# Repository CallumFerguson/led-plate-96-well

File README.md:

# led-plate-96-well

control genetically engineered cells with light

## Description

PCB for running optogenetic experiments. Designed to shine light through the bottom of [clear bottom 96 well plates](https://www.thermofisher.com/order/catalog/product/152037) and activate light gated ion channels in genetically engineered cells.

Used for experiments in controlling cell maturation by changing the cell's resting membrane potential.

## PCB

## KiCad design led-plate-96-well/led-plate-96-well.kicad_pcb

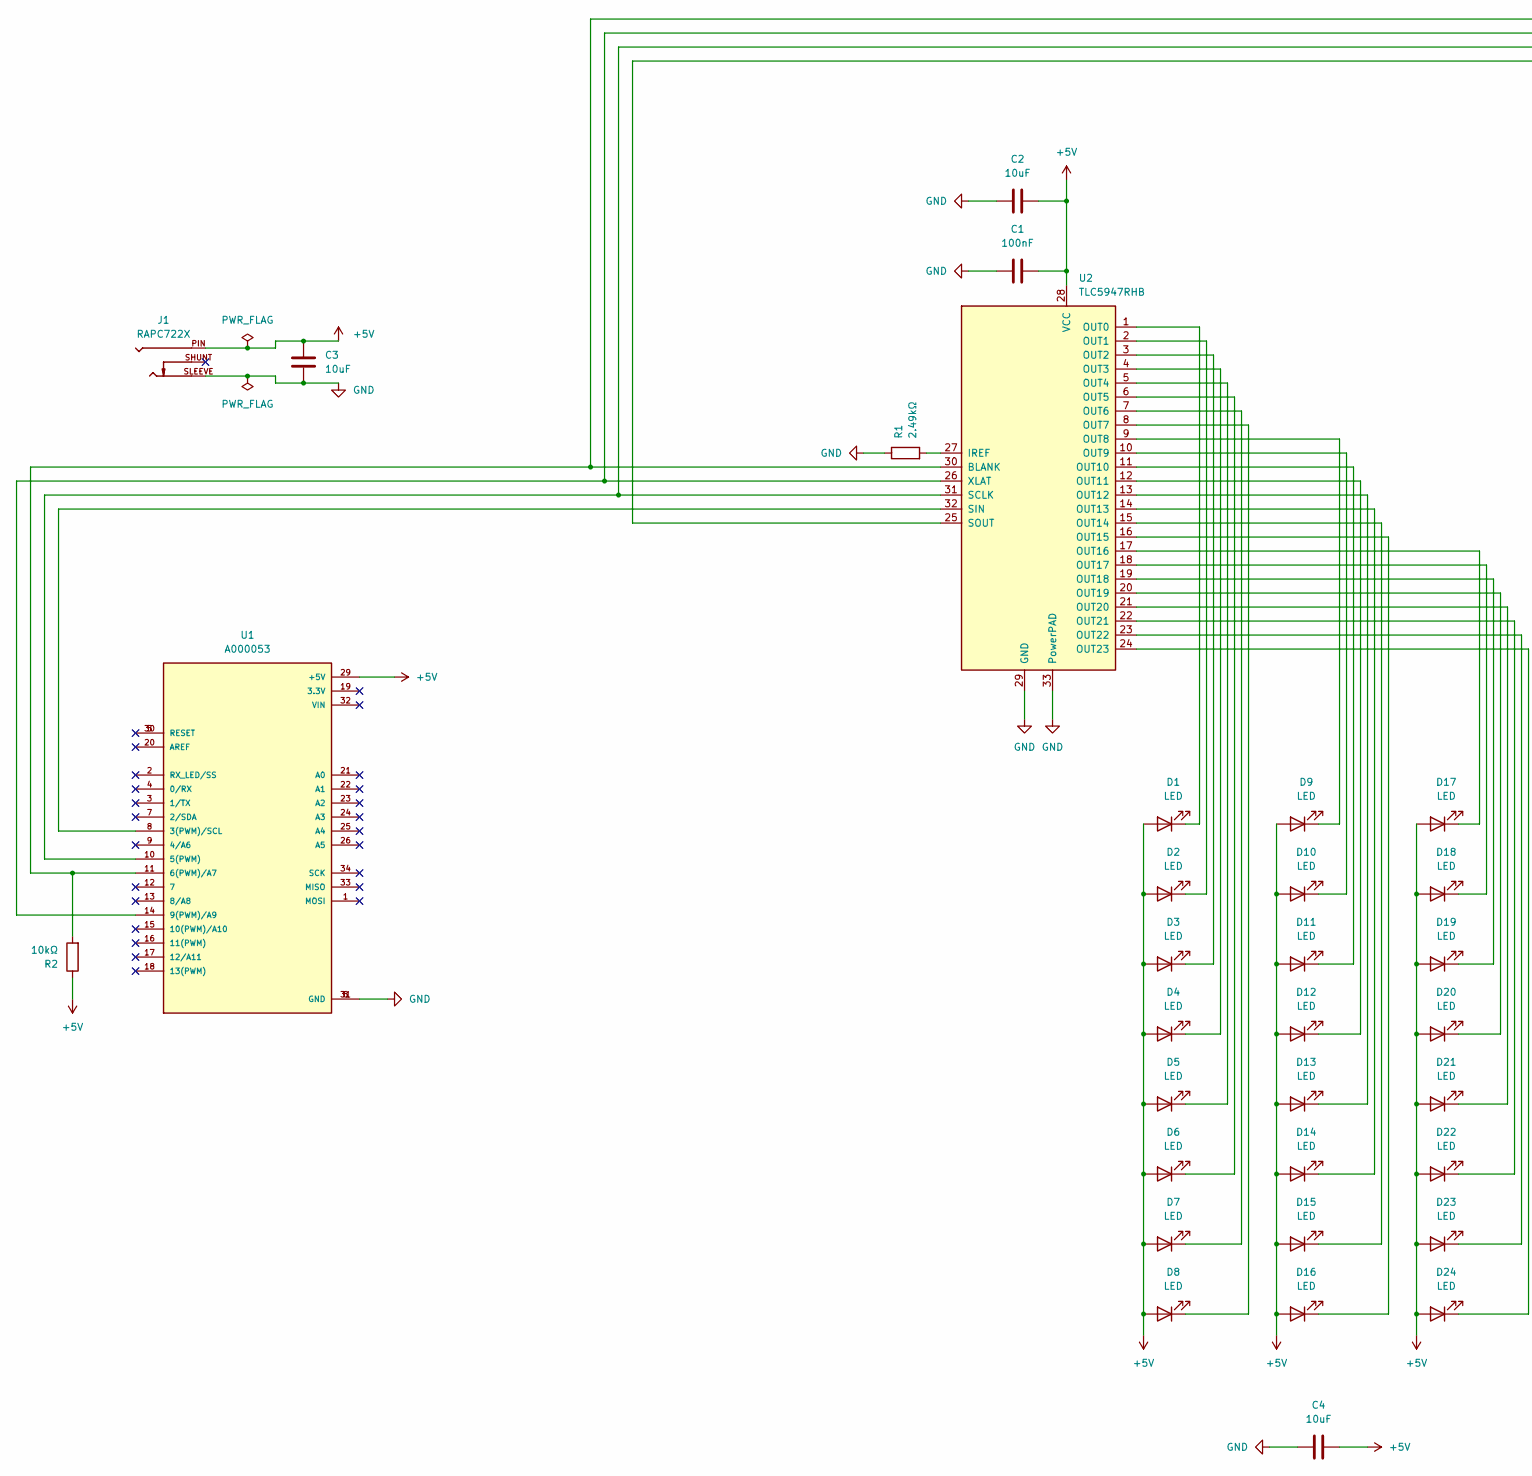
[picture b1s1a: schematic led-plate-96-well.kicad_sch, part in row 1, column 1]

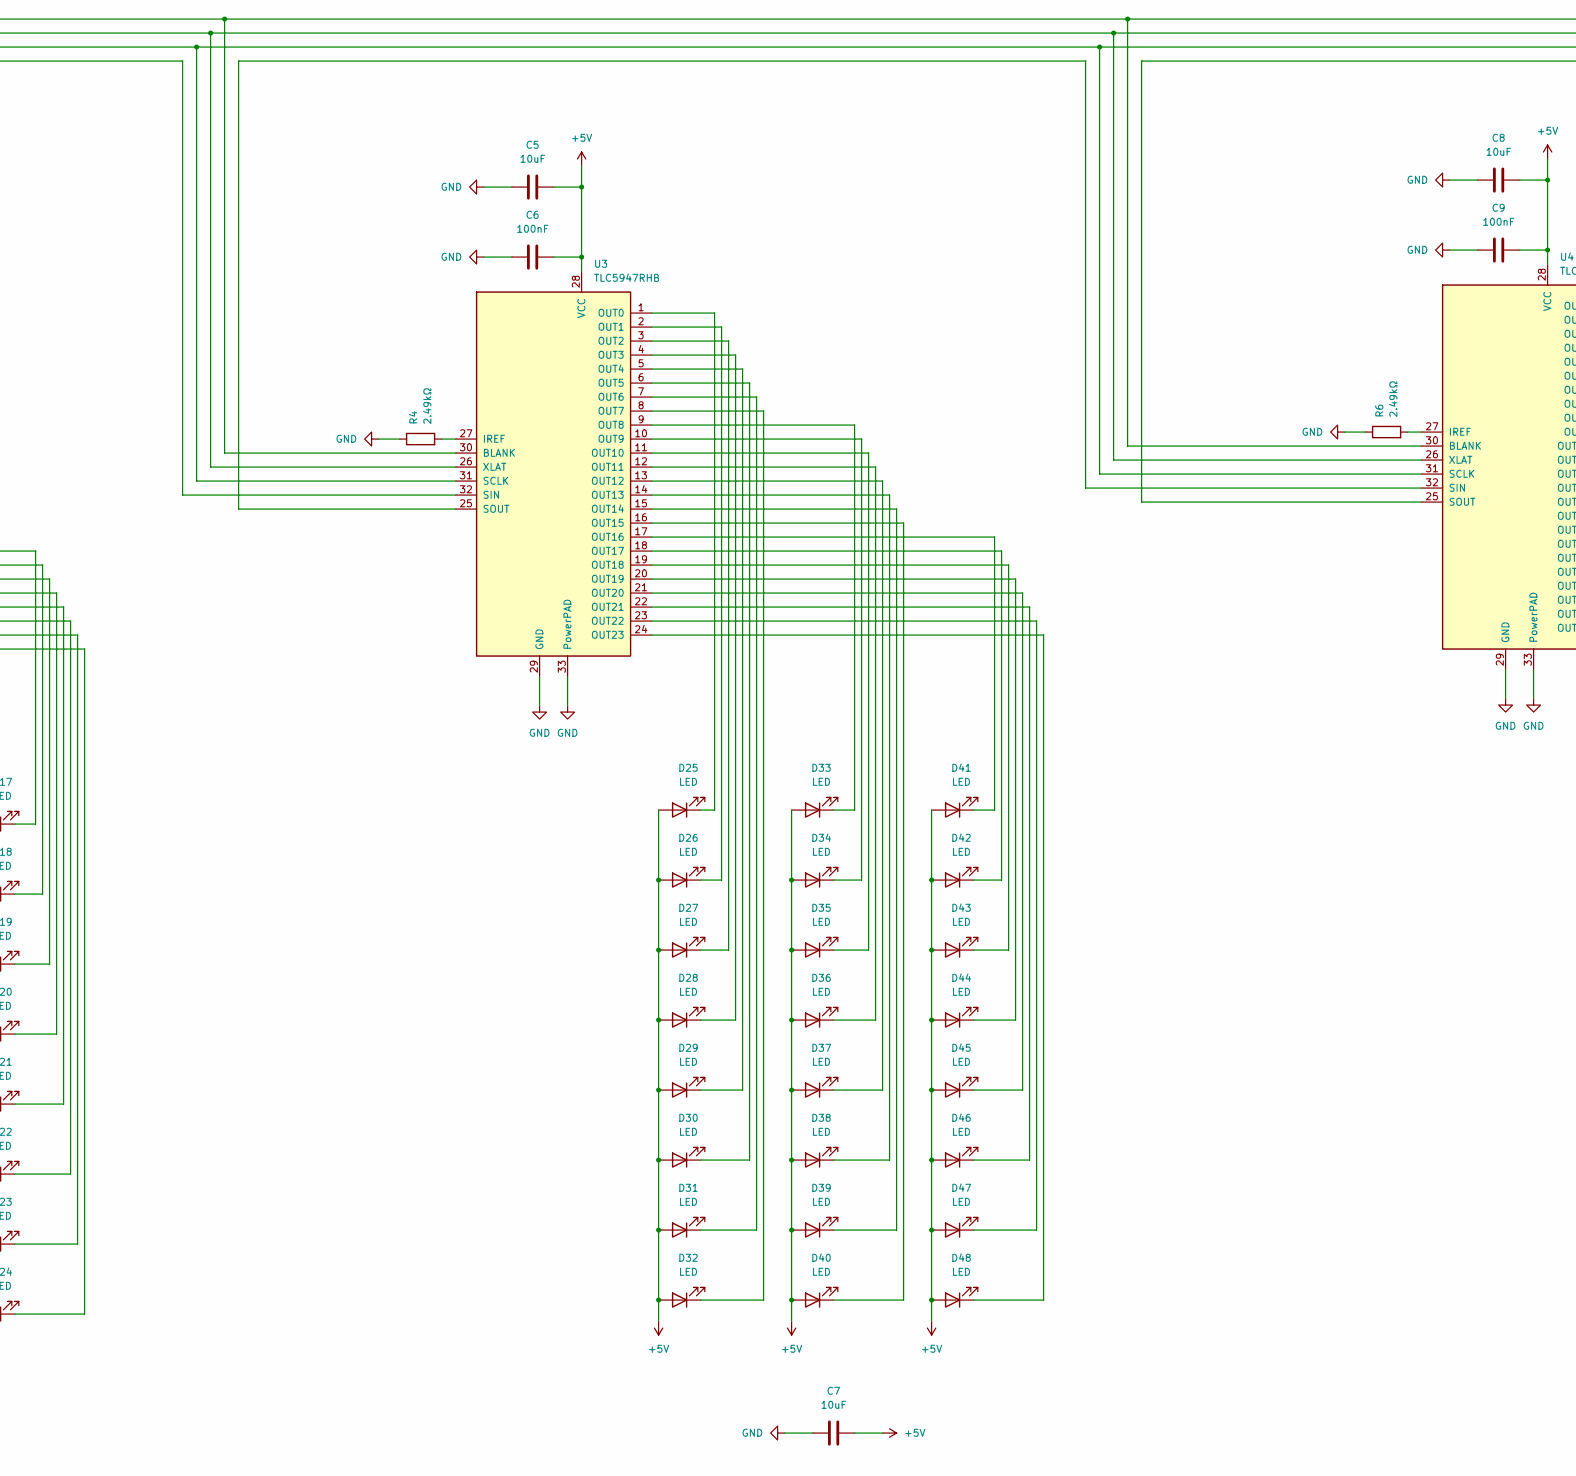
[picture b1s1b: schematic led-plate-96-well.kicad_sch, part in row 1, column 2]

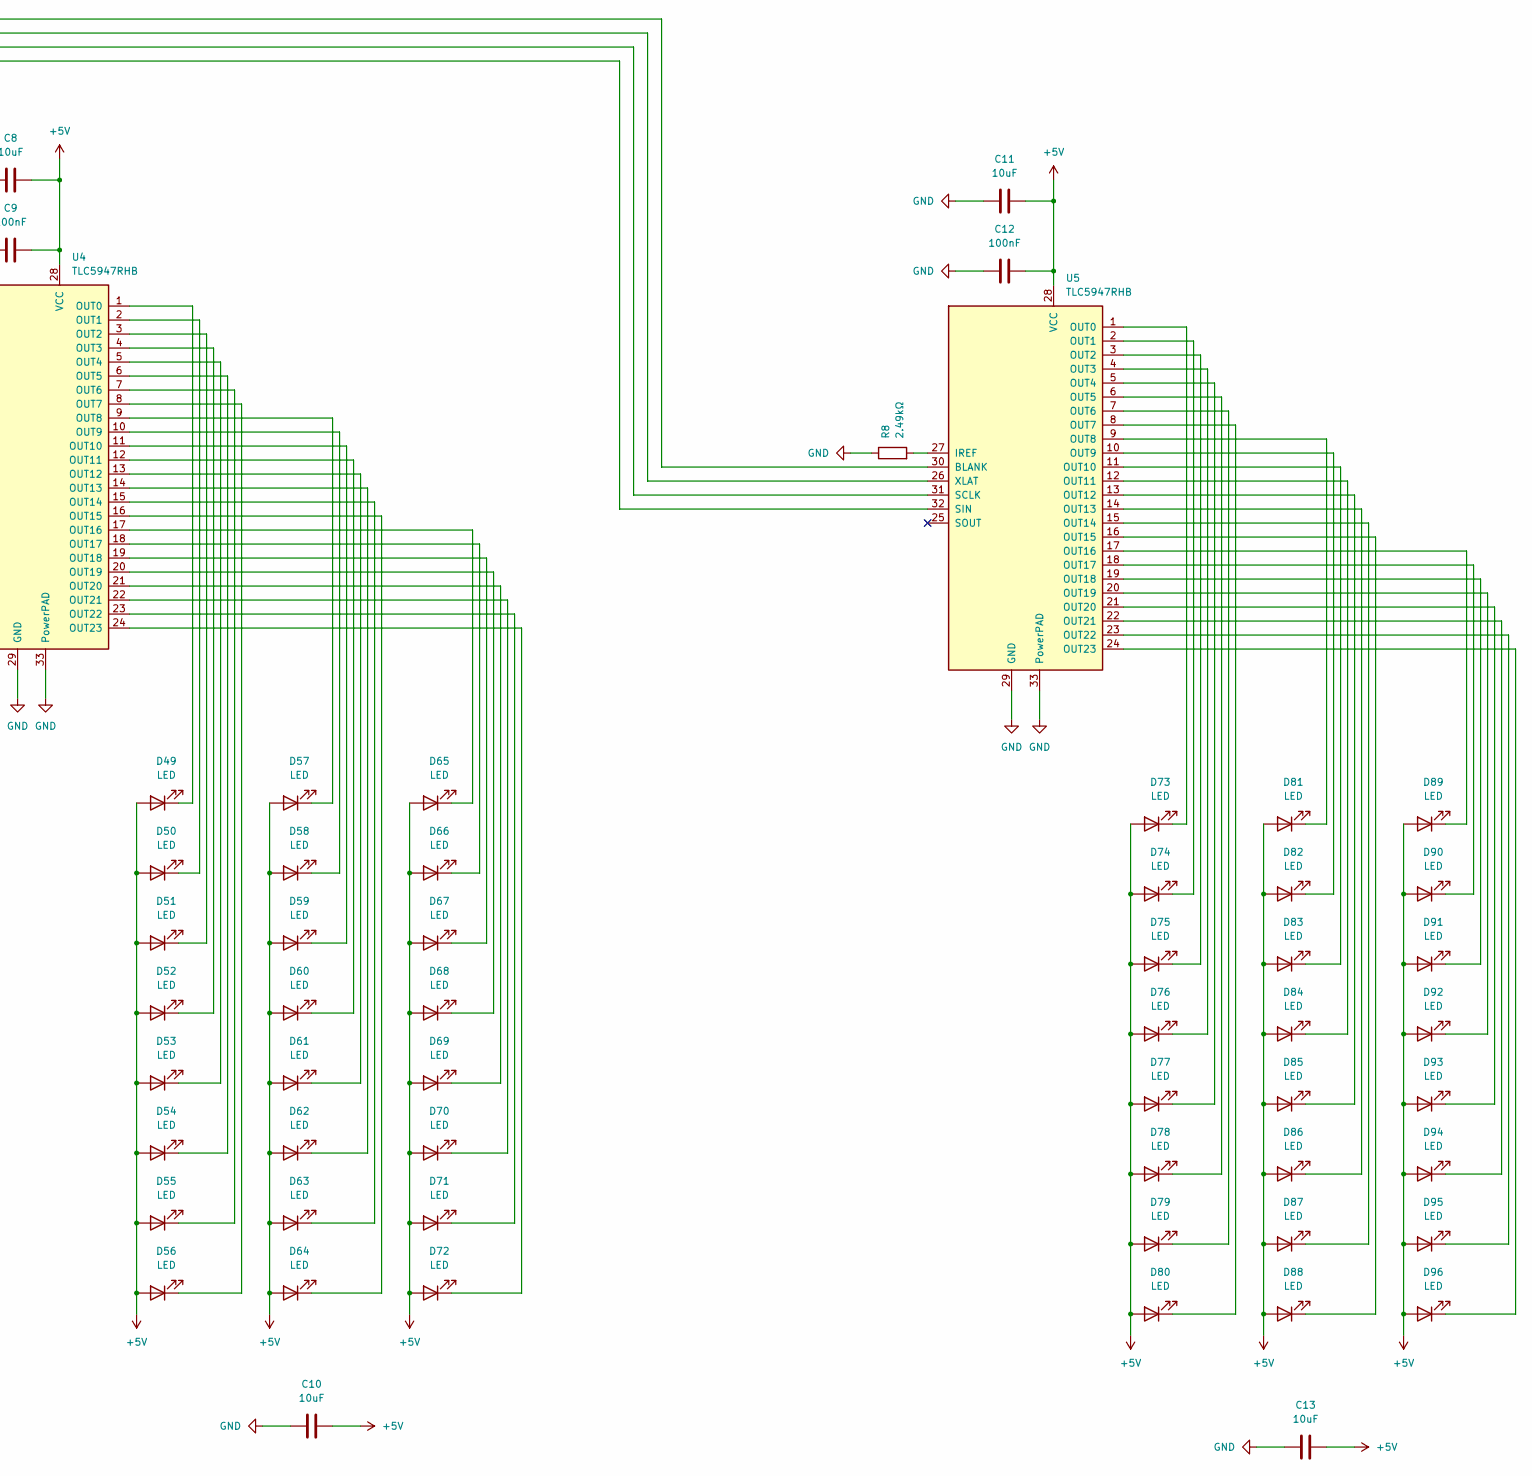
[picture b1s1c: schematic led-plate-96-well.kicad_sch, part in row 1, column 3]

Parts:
C1, C6, C9, C12: 100nF; C_0603_1608Metric; part number CC0603KRX7R9BB104
C2, C3, C4, C5, C7, C8, C10, C11, C13: 10uF; C_0805_2012Metric; part number CL21A106KAYNNNE
D1, D2, D3, D4, D5, D6, D7, D8, D9, D10, D11, D12, D13, D14, D15, D16, D17, D18, D19, D20, D21, D22, D23, D24, D25, D26, D27, D28, D29, D30, D31, D32, D33, D34, D35, D36, D37, D38, D39, D40, D41, D42, D43, D44, D45, D46, D47, D48, D49, D50, D51, D52, D53, D54, D55, D56, D57, D58, D59, D60, D61, D62, D63, D64, D65, D66, D67, D68, D69, D70, D71, D72, D73, D74, D75, D76, D77, D78, D79, D80, D81, D82, D83, D84, D85, D86, D87, D88, D89, D90, D91, D92, D93, D94, D95, D96: LED; LED_PLCC_2835; part number TJ-S2835UG2W8TLC6B-A5
J1: RAPC722X; SWITCHCRAFT_RAPC722X; PARTREV A
R1, R4, R6, R8: 2.49kΩ; R_0603_1608Metric; part number RC0603FR-072K49L
R2: 10kΩ; R_0603_1608Metric; part number 0603WAF1002T5E
U1: A000053; PARTREV N/A
U2, U3, U4, U5: TLC5947RHB; QFN-32-1EP_5x5mm_P0.5mm_EP3.45x3.45mm

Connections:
+5V: C1.2, C2.2, C3.1, C4.2, C5.2, C6.2, C7.2, C8.2, C9.2, C10.2, C11.2, C12.2, C13.2, D1.2 (A), D2.2 (A), D3.2 (A), D4.2 (A), D5.2 (A), D6.2 (A), D7.2 (A), D8.2 (A), D9.2 (A), D10.2 (A), D11.2 (A), D12.2 (A), D13.2 (A), D14.2 (A), D15.2 (A), D16.2 (A), D17.2 (A), D18.2 (A), D19.2 (A), D20.2 (A), D21.2 (A), D22.2 (A), D23.2 (A), D24.2 (A), D25.2 (A), D26.2 (A), D27.2 (A), D28.2 (A), D29.2 (A), D30.2 (A), D31.2 (A), D32.2 (A), D33.2 (A), D34.2 (A), D35.2 (A), D36.2 (A), D37.2 (A), D38.2 (A), D39.2 (A), D40.2 (A), D41.2 (A), D42.2 (A), D43.2 (A), D44.2 (A), D45.2 (A), D46.2 (A), D47.2 (A), D48.2 (A), D49.2 (A), D50.2 (A), D51.2 (A), D52.2 (A), D53.2 (A), D54.2 (A), D55.2 (A), D56.2 (A), D57.2 (A), D58.2 (A), D59.2 (A), D60.2 (A), D61.2 (A), D62.2 (A), D63.2 (A), D64.2 (A), D65.2 (A), D66.2 (A), D67.2 (A), D68.2 (A), D69.2 (A), D70.2 (A), D71.2 (A), D72.2 (A), D73.2 (A), D74.2 (A), D75.2 (A), D76.2 (A), D77.2 (A), D78.2 (A), D79.2 (A), D80.2 (A), D81.2 (A), D82.2 (A), D83.2 (A), D84.2 (A), D85.2 (A), D86.2 (A), D87.2 (A), D88.2 (A), D89.2 (A), D90.2 (A), D91.2 (A), D92.2 (A), D93.2 (A), D94.2 (A), D95.2 (A), D96.2 (A), J1.PIN, R2.1, U1.29 (+5V), U2.28 (VCC), U3.28 (VCC), U4.28 (VCC), U5.28 (VCC)
GND: C1.1, C2.1, C3.2, C4.1, C5.1, C6.1, C7.1, C8.1, C9.1, C10.1, C11.1, C12.1, C13.1, J1.SLEEVE, R1.1, R4.1, R6.1, R8.1, U1.6 (GND), U1.31 (GND), U2.29 (GND), U2.33 (PowerPAD), U3.29 (GND), U3.33 (PowerPAD), U4.29 (GND), U4.33 (PowerPAD), U5.29 (GND), U5.33 (PowerPAD)
unnamed: D1.1 (K), U2.1 (OUT0)
unnamed: D2.1 (K), U2.2 (OUT1)
unnamed: D3.1 (K), U2.3 (OUT2)
unnamed: D4.1 (K), U2.4 (OUT3)
unnamed: D5.1 (K), U2.5 (OUT4)
unnamed: D6.1 (K), U2.6 (OUT5)
unnamed: D7.1 (K), U2.7 (OUT6)
unnamed: D8.1 (K), U2.8 (OUT7)
unnamed: D9.1 (K), U2.9 (OUT8)
unnamed: D10.1 (K), U2.10 (OUT9)
unnamed: D11.1 (K), U2.11 (OUT10)
unnamed: D12.1 (K), U2.12 (OUT11)
unnamed: D13.1 (K), U2.13 (OUT12)
unnamed: D14.1 (K), U2.14 (OUT13)
unnamed: D15.1 (K), U2.15 (OUT14)
unnamed: D16.1 (K), U2.16 (OUT15)
unnamed: D17.1 (K), U2.17 (OUT16)
unnamed: D18.1 (K), U2.18 (OUT17)
unnamed: D19.1 (K), U2.19 (OUT18)
unnamed: D20.1 (K), U2.20 (OUT19)
unnamed: D21.1 (K), U2.21 (OUT20)
unnamed: D22.1 (K), U2.22 (OUT21)
unnamed: D23.1 (K), U2.23 (OUT22)
unnamed: D24.1 (K), U2.24 (OUT23)
unnamed: D25.1 (K), U3.1 (OUT0)
unnamed: D26.1 (K), U3.2 (OUT1)
unnamed: D27.1 (K), U3.3 (OUT2)
unnamed: D28.1 (K), U3.4 (OUT3)
unnamed: D29.1 (K), U3.5 (OUT4)
unnamed: D30.1 (K), U3.6 (OUT5)
unnamed: D31.1 (K), U3.7 (OUT6)
unnamed: D32.1 (K), U3.8 (OUT7)
unnamed: D33.1 (K), U3.9 (OUT8)
unnamed: D34.1 (K), U3.10 (OUT9)
unnamed: D35.1 (K), U3.11 (OUT10)
unnamed: D36.1 (K), U3.12 (OUT11)
unnamed: D37.1 (K), U3.13 (OUT12)
unnamed: D38.1 (K), U3.14 (OUT13)
unnamed: D39.1 (K), U3.15 (OUT14)
unnamed: D40.1 (K), U3.16 (OUT15)
unnamed: D41.1 (K), U3.17 (OUT16)
unnamed: D42.1 (K), U3.18 (OUT17)
unnamed: D43.1 (K), U3.19 (OUT18)
unnamed: D44.1 (K), U3.20 (OUT19)
unnamed: D45.1 (K), U3.21 (OUT20)
unnamed: D46.1 (K), U3.22 (OUT21)
unnamed: D47.1 (K), U3.23 (OUT22)
unnamed: D48.1 (K), U3.24 (OUT23)
unnamed: D49.1 (K), U4.1 (OUT0)
unnamed: D50.1 (K), U4.2 (OUT1)
unnamed: D51.1 (K), U4.3 (OUT2)
unnamed: D52.1 (K), U4.4 (OUT3)
unnamed: D53.1 (K), U4.5 (OUT4)
unnamed: D54.1 (K), U4.6 (OUT5)
unnamed: D55.1 (K), U4.7 (OUT6)
unnamed: D56.1 (K), U4.8 (OUT7)
unnamed: D57.1 (K), U4.9 (OUT8)
unnamed: D58.1 (K), U4.10 (OUT9)
unnamed: D59.1 (K), U4.11 (OUT10)
unnamed: D60.1 (K), U4.12 (OUT11)
unnamed: D61.1 (K), U4.13 (OUT12)
unnamed: D62.1 (K), U4.14 (OUT13)
unnamed: D63.1 (K), U4.15 (OUT14)
unnamed: D64.1 (K), U4.16 (OUT15)
unnamed: D65.1 (K), U4.17 (OUT16)
unnamed: D66.1 (K), U4.18 (OUT17)
unnamed: D67.1 (K), U4.19 (OUT18)
unnamed: D68.1 (K), U4.20 (OUT19)
unnamed: D69.1 (K), U4.21 (OUT20)
unnamed: D70.1 (K), U4.22 (OUT21)
unnamed: D71.1 (K), U4.23 (OUT22)
unnamed: D72.1 (K), U4.24 (OUT23)
unnamed: D73.1 (K), U5.1 (OUT0)
unnamed: D74.1 (K), U5.2 (OUT1)
unnamed: D75.1 (K), U5.3 (OUT2)
unnamed: D76.1 (K), U5.4 (OUT3)
unnamed: D77.1 (K), U5.5 (OUT4)
unnamed: D78.1 (K), U5.6 (OUT5)
unnamed: D79.1 (K), U5.7 (OUT6)
unnamed: D80.1 (K), U5.8 (OUT7)
unnamed: D81.1 (K), U5.9 (OUT8)
unnamed: D82.1 (K), U5.10 (OUT9)
unnamed: D83.1 (K), U5.11 (OUT10)
unnamed: D84.1 (K), U5.12 (OUT11)
unnamed: D85.1 (K), U5.13 (OUT12)
unnamed: D86.1 (K), U5.14 (OUT13)
unnamed: D87.1 (K), U5.15 (OUT14)
unnamed: D88.1 (K), U5.16 (OUT15)
unnamed: D89.1 (K), U5.17 (OUT16)
unnamed: D90.1 (K), U5.18 (OUT17)
unnamed: D91.1 (K), U5.19 (OUT18)
unnamed: D92.1 (K), U5.20 (OUT19)
unnamed: D93.1 (K), U5.21 (OUT20)
unnamed: D94.1 (K), U5.22 (OUT21)
unnamed: D95.1 (K), U5.23 (OUT22)
unnamed: D96.1 (K), U5.24 (OUT23)
unnamed: U1.8 (3(PWM)/SCL), U2.32 (SIN)
unnamed: U1.10 (5(PWM)), U2.31 (SCLK), U3.31 (SCLK), U4.31 (SCLK), U5.31 (SCLK)
unnamed: R2.2, U1.11 (6(PWM)/A7), U2.30 (BLANK), U3.30 (BLANK), U4.30 (BLANK), U5.30 (BLANK)
unnamed: U1.14 (9(PWM)/A9), U2.26 (XLAT), U3.26 (XLAT), U4.26 (XLAT), U5.26 (XLAT)
unnamed: R1.2, U2.27 (IREF)
unnamed: U2.25 (SOUT), U3.32 (SIN)
unnamed: R4.2, U3.27 (IREF)
unnamed: U3.25 (SOUT), U4.32 (SIN)
unnamed: R6.2, U4.27 (IREF)
unnamed: U4.25 (SOUT), U5.32 (SIN)
unnamed: R8.2, U5.27 (IREF)

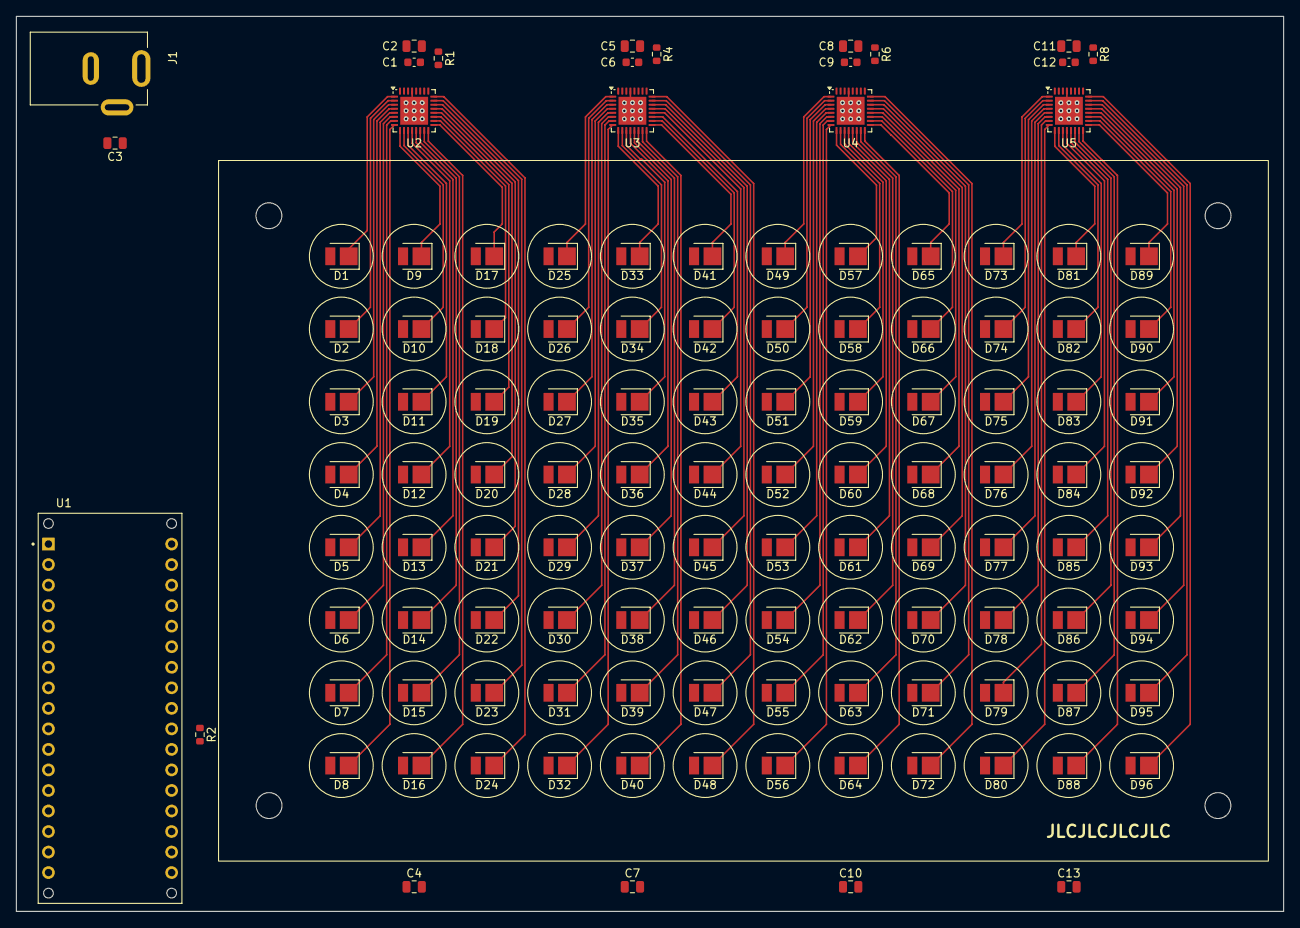
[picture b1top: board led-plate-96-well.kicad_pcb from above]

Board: 2 copper layers, 156.8 x 110.7 mm, 120 parts (0 on the bottom side), 109 nets.

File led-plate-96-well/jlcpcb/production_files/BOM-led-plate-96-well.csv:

Comment,Designator,Footprint,LCSC,Quantity
2.49kΩ,"R1,R4,R6,R8",R_0402_1005Metric,C102924,4
100nF,"C1,C12,C6,C9",C_0603_1608Metric,C14663,4
100uF,C3,C_1206_3216Metric,C15008,1
10uF,"C10,C11,C13,C2,C4,C5,C7,C8",C_0805_2012Metric,C15850,8
TLC5947RHB,"U2,U3,U4,U5",QFN-32-1EP_5x5mm_P0.5mm_EP3.45x3.45mm,C181402,4
10kΩ,R2,R_0603_1608Metric,C25804,1
LED,"D1,D10,D11,D12,D13,D14,D15,D16,D17,D18,D19,D2,D20,D21,D22,D23,D24,D25,D26,D27,D28,D29,D3,D30,D31,D32,D33,D34,D35,D36,D37,D38,D39,D4,D40,D41,D42,D43,D44,D45,D46,D47,D48,D49,D5,D50,D51,D52,D53,D54,D55,D56,D57,D58,D59,D6,D60,D61,D62,D63,D64,D65,D66,D67,D68,D69,D7,D70,D71,D72,D73,D74,D75,D76,D77,D78,D79,D8,D80,D81,D82,D83,D84,D85,D86,D87,D88,D89,D9,D90,D91,D92,D93,D94,D95,D96",LED_PLCC_2835,C440449,96

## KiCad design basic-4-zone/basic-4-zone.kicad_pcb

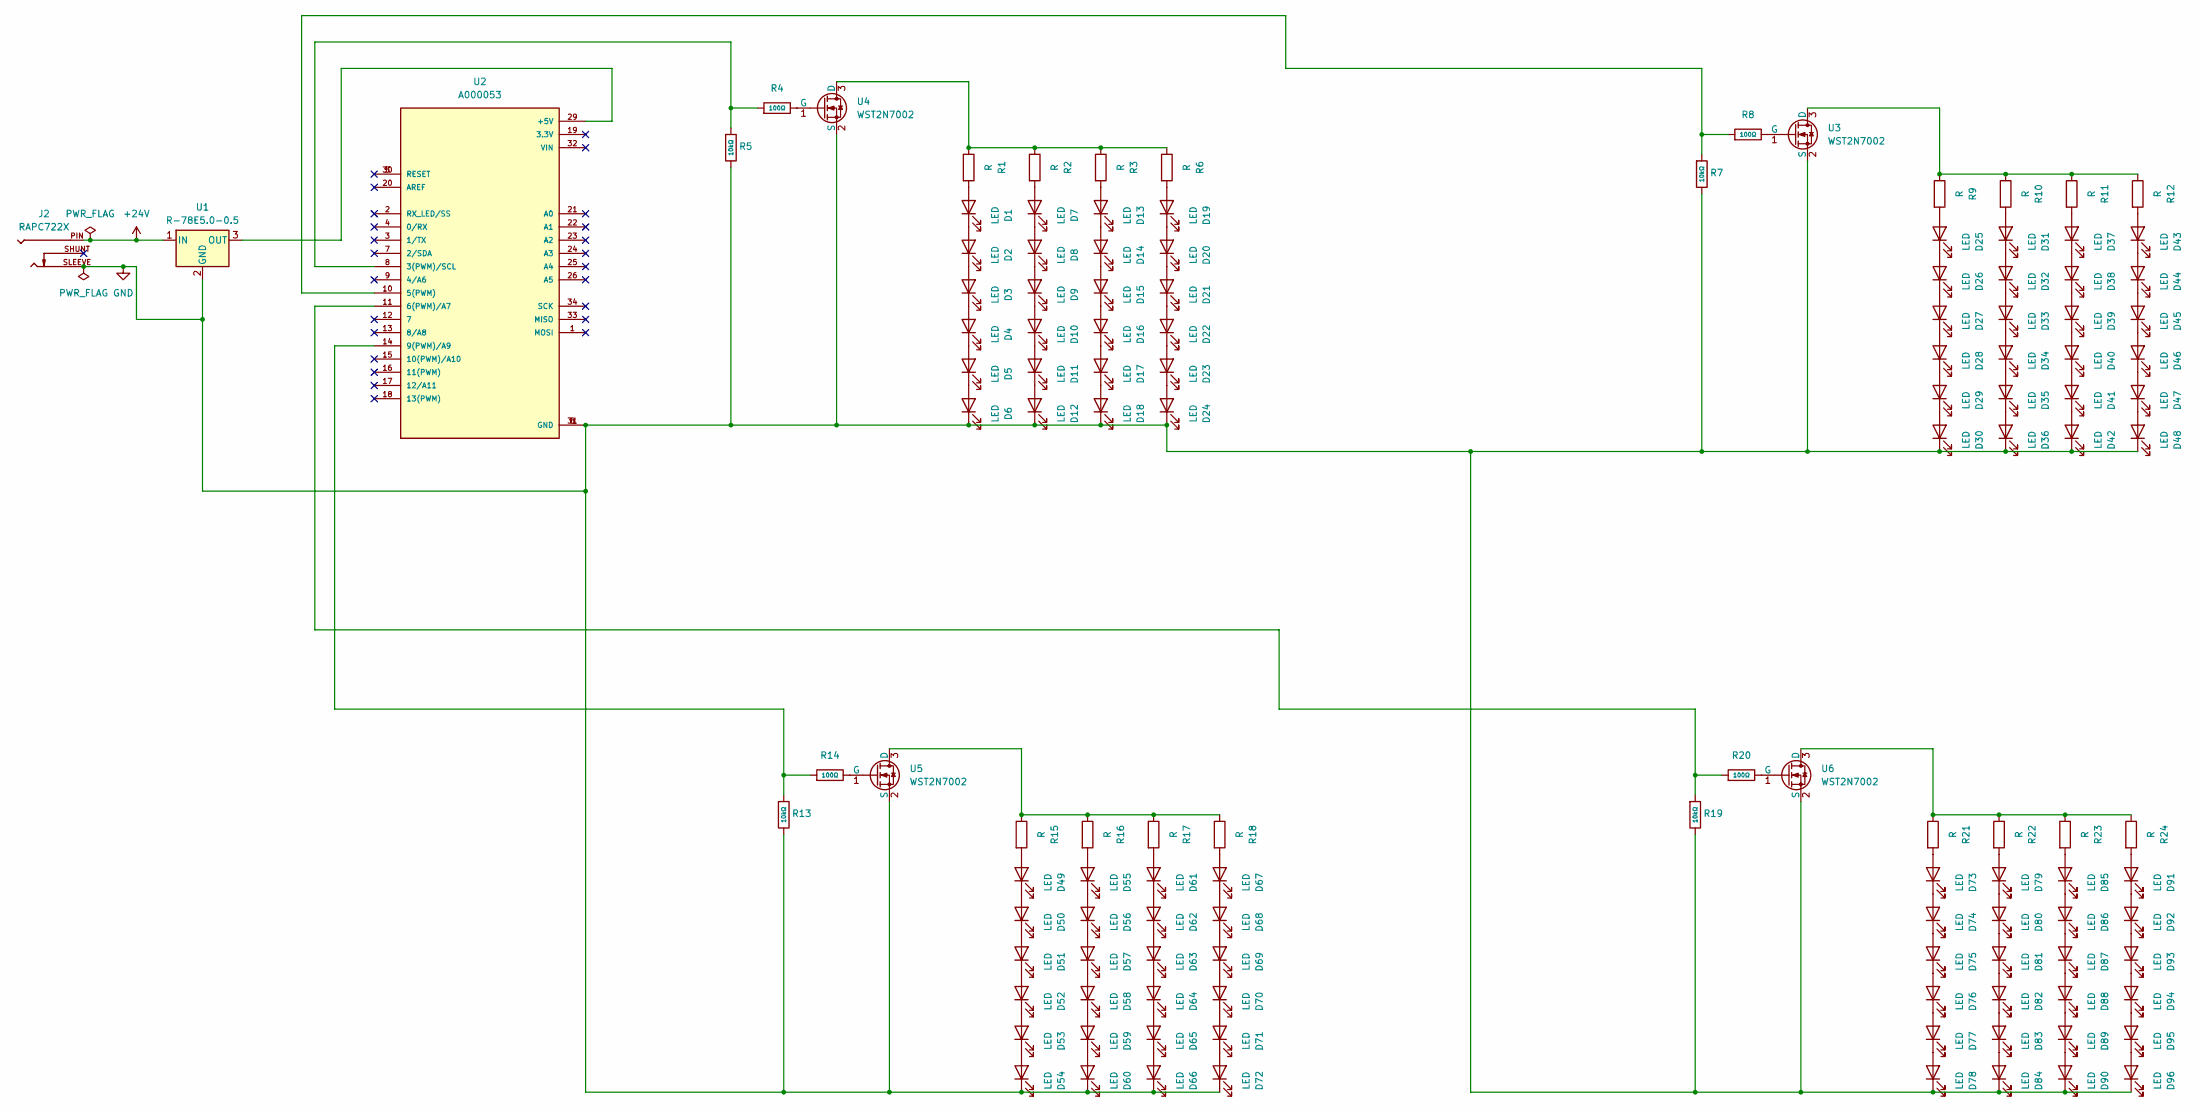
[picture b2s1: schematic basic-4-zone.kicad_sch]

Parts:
D1, D2, D3, D4, D5, D6, D7, D8, D9, D10, D11, D12, D13, D14, D15, D16, D17, D18, D19, D20, D21, D22, D23, D24, D25, D26, D27, D28, D29, D30, D31, D32, D33, D34, D35, D36, D37, D38, D39, D40, D41, D42, D43, D44, D45, D46, D47, D48, D49, D50, D51, D52, D53, D54, D55, D56, D57, D58, D59, D60, D61, D62, D63, D64, D65, D66, D67, D68, D69, D70, D71, D72, D73, D74, D75, D76, D77, D78, D79, D80, D81, D82, D83, D84, D85, D86, D87, D88, D89, D90, D91, D92, D93, D94, D95, D96: LED; LED_Luminus_MP-3030-1100_3.0x3.0mm
J2: RAPC722X; SWITCHCRAFT_RAPC722X; PARTREV A
R1, R2, R3, R6, R9, R10, R11, R12, R15, R16, R17, R18, R21, R22, R23, R24: R; R_1210_3225Metric
R4, R8, R14, R20: 100Ω; R_1206; Overload Voltage (Max) 200V; Tolerance ±1%; Part 1206W4F100LT5E; LCSC C25334
R5, R7, R13, R19: 10kΩ; R_1206; Overload Voltage (Max) 200V; Tolerance ±1%; Part 1206W4F1002T5E; LCSC C17902
U1: R-78E5.0-0.5; Converter_DCDC_RECOM_R-78E-0.5_THT
U2: A000053; ARDUINO_A000053; PARTREV N/A
U3, U4, U5, U6: WST2N7002; SOT-23

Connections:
+24V: J2.PIN, U1.1 (IN)
GND: D6.1 (K), D12.1 (K), D18.1 (K), D24.1 (K), D30.1 (K), D36.1 (K), D42.1 (K), D48.1 (K), D54.1 (K), D60.1 (K), D66.1 (K), D72.1 (K), D78.1 (K), D84.1 (K), D90.1 (K), D96.1 (K), J2.SLEEVE, R5.2, R7.2, R13.2, R19.2, U1.2 (GND), U2.6 (GND), U2.31 (GND), U3.2 (S), U4.2 (S), U5.2 (S), U6.2 (S)
unnamed: D1.2 (A), R1.2
unnamed: D1.1 (K), D2.2 (A)
unnamed: D2.1 (K), D3.2 (A)
unnamed: D3.1 (K), D4.2 (A)
unnamed: D4.1 (K), D5.2 (A)
unnamed: D5.1 (K), D6.2 (A)
unnamed: D7.2 (A), R2.2
unnamed: D7.1 (K), D8.2 (A)
unnamed: D8.1 (K), D9.2 (A)
unnamed: D9.1 (K), D10.2 (A)
unnamed: D10.1 (K), D11.2 (A)
unnamed: D11.1 (K), D12.2 (A)
unnamed: D13.2 (A), R3.2
unnamed: D13.1 (K), D14.2 (A)
unnamed: D14.1 (K), D15.2 (A)
unnamed: D15.1 (K), D16.2 (A)
unnamed: D16.1 (K), D17.2 (A)
unnamed: D17.1 (K), D18.2 (A)
unnamed: D19.2 (A), R6.2
unnamed: D19.1 (K), D20.2 (A)
unnamed: D20.1 (K), D21.2 (A)
unnamed: D21.1 (K), D22.2 (A)
unnamed: D22.1 (K), D23.2 (A)
unnamed: D23.1 (K), D24.2 (A)
unnamed: D25.2 (A), R9.2
unnamed: D25.1 (K), D26.2 (A)
unnamed: D26.1 (K), D27.2 (A)
unnamed: D27.1 (K), D28.2 (A)
unnamed: D28.1 (K), D29.2 (A)
unnamed: D29.1 (K), D30.2 (A)
unnamed: D31.2 (A), R10.2
unnamed: D31.1 (K), D32.2 (A)
unnamed: D32.1 (K), D33.2 (A)
unnamed: D33.1 (K), D34.2 (A)
unnamed: D34.1 (K), D35.2 (A)
unnamed: D35.1 (K), D36.2 (A)
unnamed: D37.2 (A), R11.2
unnamed: D37.1 (K), D38.2 (A)
unnamed: D38.1 (K), D39.2 (A)
unnamed: D39.1 (K), D40.2 (A)
unnamed: D40.1 (K), D41.2 (A)
unnamed: D41.1 (K), D42.2 (A)
unnamed: D43.2 (A), R12.2
unnamed: D43.1 (K), D44.2 (A)
unnamed: D44.1 (K), D45.2 (A)
unnamed: D45.1 (K), D46.2 (A)
unnamed: D46.1 (K), D47.2 (A)
unnamed: D47.1 (K), D48.2 (A)
unnamed: D49.2 (A), R15.2
unnamed: D49.1 (K), D50.2 (A)
unnamed: D50.1 (K), D51.2 (A)
unnamed: D51.1 (K), D52.2 (A)
unnamed: D52.1 (K), D53.2 (A)
unnamed: D53.1 (K), D54.2 (A)
unnamed: D55.2 (A), R16.2
unnamed: D55.1 (K), D56.2 (A)
unnamed: D56.1 (K), D57.2 (A)
unnamed: D57.1 (K), D58.2 (A)
unnamed: D58.1 (K), D59.2 (A)
unnamed: D59.1 (K), D60.2 (A)
unnamed: D61.2 (A), R17.2
unnamed: D61.1 (K), D62.2 (A)
unnamed: D62.1 (K), D63.2 (A)
unnamed: D63.1 (K), D64.2 (A)
unnamed: D64.1 (K), D65.2 (A)
unnamed: D65.1 (K), D66.2 (A)
unnamed: D67.2 (A), R18.2
unnamed: D67.1 (K), D68.2 (A)
unnamed: D68.1 (K), D69.2 (A)
unnamed: D69.1 (K), D70.2 (A)
unnamed: D70.1 (K), D71.2 (A)
unnamed: D71.1 (K), D72.2 (A)
unnamed: D73.2 (A), R21.2
unnamed: D73.1 (K), D74.2 (A)
unnamed: D74.1 (K), D75.2 (A)
unnamed: D75.1 (K), D76.2 (A)
unnamed: D76.1 (K), D77.2 (A)
unnamed: D77.1 (K), D78.2 (A)
unnamed: D79.2 (A), R22.2
unnamed: D79.1 (K), D80.2 (A)
unnamed: D80.1 (K), D81.2 (A)
unnamed: D81.1 (K), D82.2 (A)
unnamed: D82.1 (K), D83.2 (A)
unnamed: D83.1 (K), D84.2 (A)
unnamed: D85.2 (A), R23.2
unnamed: D85.1 (K), D86.2 (A)
unnamed: D86.1 (K), D87.2 (A)
unnamed: D87.1 (K), D88.2 (A)
unnamed: D88.1 (K), D89.2 (A)
unnamed: D89.1 (K), D90.2 (A)
unnamed: D91.2 (A), R24.2
unnamed: D91.1 (K), D92.2 (A)
unnamed: D92.1 (K), D93.2 (A)
unnamed: D93.1 (K), D94.2 (A)
unnamed: D94.1 (K), D95.2 (A)
unnamed: D95.1 (K), D96.2 (A)
unnamed: U1.3 (OUT), U2.29 (+5V)
unnamed: R4.1, R5.1, U2.8 (3(PWM)/SCL)
unnamed: R7.1, R8.1, U2.10 (5(PWM))
unnamed: R19.1, R20.1, U2.11 (6(PWM)/A7)
unnamed: R13.1, R14.1, U2.14 (9(PWM)/A9)
unnamed: R9.1, R10.1, R11.1, R12.1, U3.3 (D)
unnamed: R8.2, U3.1 (G)
unnamed: R1.1, R2.1, R3.1, R6.1, U4.3 (D)
unnamed: R4.2, U4.1 (G)
unnamed: R15.1, R16.1, R17.1, R18.1, U5.3 (D)
unnamed: R14.2, U5.1 (G)
unnamed: R21.1, R22.1, R23.1, R24.1, U6.3 (D)
unnamed: R20.2, U6.1 (G)

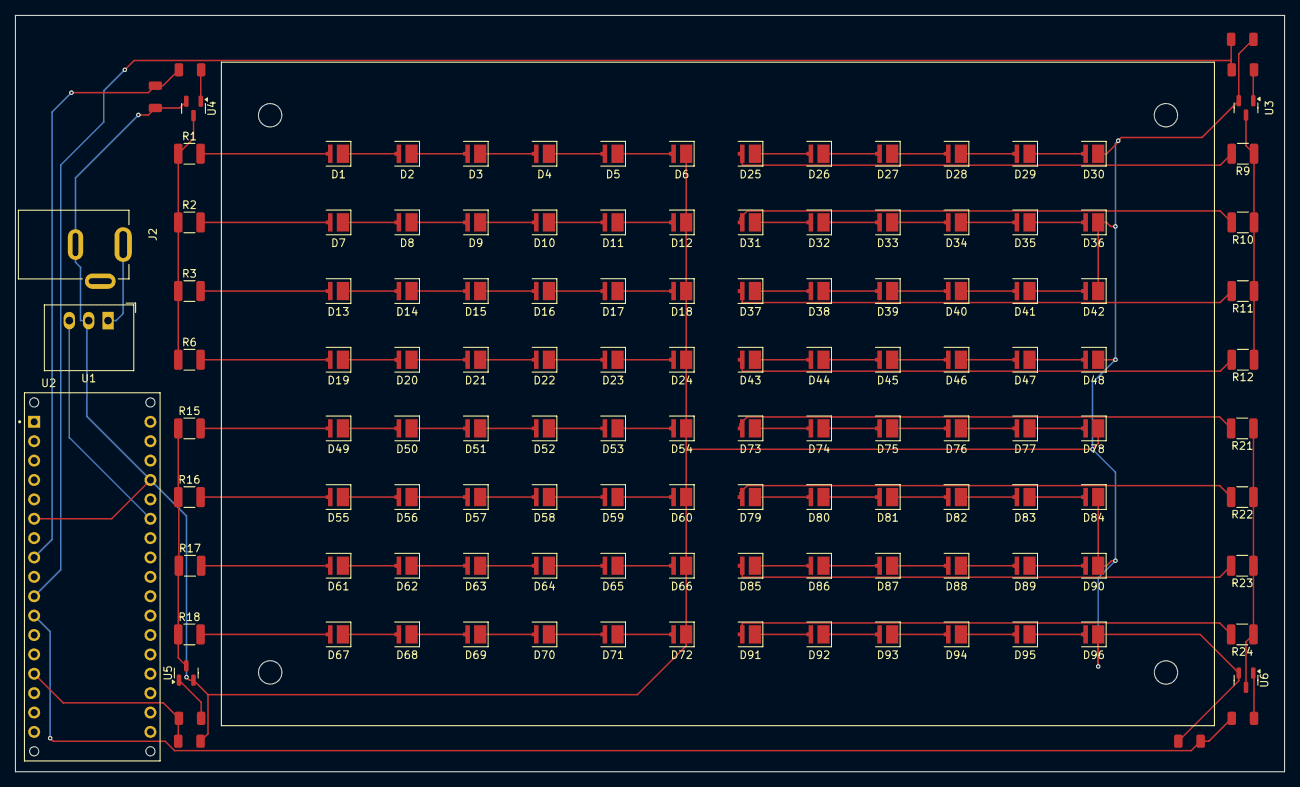
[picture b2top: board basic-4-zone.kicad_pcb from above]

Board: 2 copper layers, 166.3 x 99.1 mm, 127 parts (0 on the bottom side), 111 nets.

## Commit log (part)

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2025-06-24 add project
2025-06-25 basic led layout started
2025-06-25 all 96 leds laid out
2025-06-25 basic pcb layout done
2025-06-25 auto route done
2025-06-25 drill holes, make more compact, re-route
2025-06-25 remove right angle
2025-06-25 build gerbers
2025-06-26 set components and build again
2025-06-26 rename project and add second project
2025-06-26 create basic test pcb
2025-06-26 fix ciruit
2025-06-26 re route
2025-06-26 build
2025-07-02 fix label position
2025-07-07 create main project
2025-07-10 start main board
2025-07-10 layout leds
2025-07-11 basic layout for all components
2025-07-11 finished routing traces
2025-07-11 assign parts and fix led driver vias
2025-07-30 fix ground vias and re order
2025-08-05 wave test sketch
2025-08-20 start redesign as 2 layer board
2025-08-20 fix some part numbers and footprints
2025-08-25 create react gui app
2025-08-25 add tailwind
2025-08-26 basic page layout
2025-08-27 add 96 well plate svg
2025-08-28 start new 96 well plate component
2025-08-28 simplify WellPlate96
2025-08-29 basic groups
2025-08-29 sequence list
2025-08-29 select wells
2025-08-29 group color
2025-08-29 make groups removable
2025-09-02 create simple example arduino program
2025-09-02 basic program export working
2025-09-03 create arudino gui template
2025-09-03 export .ino with new template
2025-09-03 change label
2025-09-04 adjust default sequence step values
2025-09-04 click to drag mostly working
2025-09-04 left click for select, right for unselect
2025-09-04 fix click to toggle well
2025-09-04 allow single well drag selections
2025-09-05 randomize wells
2025-09-05 import/export config
2025-09-05 fix styling
2025-10-07 basic arduino build servrer
2025-10-13 basic express server
2025-10-14 basic sketch upload button
